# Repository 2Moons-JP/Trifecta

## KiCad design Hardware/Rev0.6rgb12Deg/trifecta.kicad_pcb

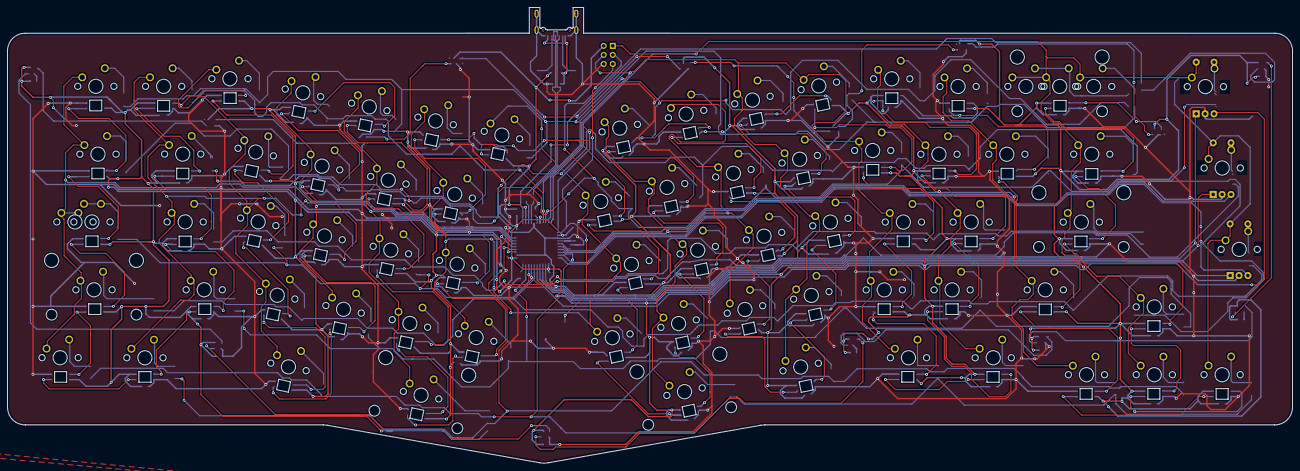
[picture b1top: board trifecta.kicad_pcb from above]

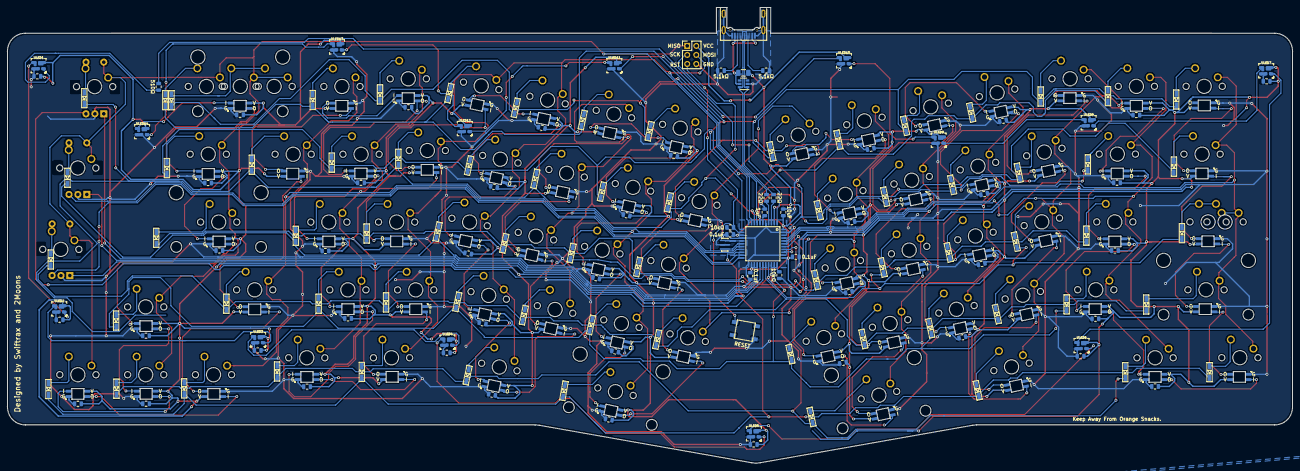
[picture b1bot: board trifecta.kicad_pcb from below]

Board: 2 copper layers, 361.0 x 128.0 mm, 285 parts (210 on the bottom side), 189 nets.

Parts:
C1: 1uF; C_0805_2012Metric
C2, C4, C6, C8, C9, C10, C11, C12, C13, C15, C18, C20, C22, C24, C26, C28, C30, C34, C36, C38, C40, C42, C44, C45, C48, C50, C52, C54, C56, C58, C60, C63, C66, C67, C69, C71, C72, C73, C74, C75, C76, C77, C78, C79: 0.1uF; C_0805_2012Metric
C16: 10uF; C_0805_2012Metric
D_1, D_2, D_3, D_4, D_5, D_6, D_7, D_8, D_9, D_10, D_11, D_12, D_13, D_15, D_16, D_17, D_18, D_19, D_20, D_21, D_22, D_23, D_24, D_25, D_26, D_27, D_28, D_29, D_30, D_31, D_33, D_34, D_35, D_36, D_37, D_38, D_39, D_40, D_41, D_42, D_43, D_44, D_45, D_46, D_47, D_48, D_49, D_50, D_51, D_52, D_53, D_54, D_55, D_56, D_57, D_58, D_59, D_60, D_61, D_62, D_63, D_64, D_65, D_66, D_67, D_68, D_69, D_70, D_71, D_72: D; D3_SMD_v2
F1: 500mA; Fuse_1206_3216Metric
J1: USB2_C_Receptacle; Mid_Mount-USB_C_HandSoldering
J2: ISP Header; PinHeader_2x03_P2.54mm_Vertical
K_1, K_2, K_3, K_4, K_5, K_6, K_7, K_8, K_9, K_10, K_11, K_12, K_13, K_14, K_16, K_18, K_19, K_20, K_21, K_22, K_23, K_24, K_25, K_26, K_27, K_28, K_29, K_30, K_31, K_34, K_35, K_36, K_37, K_38, K_39, K_40, K_41, K_42, K_43, K_44, K_46, K_48, K_49, K_50, K_51, K_52, K_53, K_54, K_55, K_56, K_57, K_58, K_60, K_61, K_70, K_71, K_72: KEYSW; MXOnly-1U-NoLED
K_15: KEYSW; MXOnly-2U-ReversedStabilizers-NoLED
K_17: KEYSW; MXOnly-1.5U-NoLED
K_32, K_33, K_59: KEYSW; MXOnly-1.75U-NoLED
K_45, K_47, K_66: KEYSW; MXOnly-2.25U-ReversedStabilizers-NoLED
K_62, K_63, K_64, K_67, K_68, K_69: KEYSW; MXOnly-1.25U-NoLED
K_65: KEYSW; MXOnly-2.75U-ReversedStabilizers-NoLED
LED1, LED2, LED3, LED4, LED5, LED6, LED7, LED8, LED9, LED10, LED11, LED12, LED13, LED15, LED17, LED18, LED19, LED20, LED21, LED22, LED23, LED24, LED25, LED26, LED27, LED28, LED29, LED30, LED33, LED34, LED35, LED36, LED37, LED38, LED39, LED40, LED41, LED42, LED43, LED44, LED45, LED47, LED48, LED49, LED50, LED51, LED52, LED53, LED54, LED55, LED56, LED57, LED58, LED59, LED60, LED62, LED63, LED64, LED65, LED66, LED67, LED68, LED69, LED70, LED71, LED72: YS-SK6812MINI-E
R1, R6: 10kΩ; R_0805_2012Metric
R2, R3: 5.1kΩ; R_0805_2012Metric
R4, R5: 22Ω; R_0805_2012Metric
R7: 510Ω; R_0805_2012Metric
SW1: RESET; SKQG-1155865
SW2, SW3, SW4: Rotary_Encoder_Switch; RotaryEncoder_EC11
U1: ATmega32U4-AU; ATMEGA32U4-AU
U2: SRV05-4; SOT-23-6
ULED1, ULED2, ULED3, ULED4, ULED5, ULED6, ULED7, ULED8, ULED9, ULED10, ULED11, ULED12, ULED13, ULED14: WS2812B-MINI; SK6812_Mini
Y1: 16MHz; Resonator_SMD_muRata_CSTxExxV-3Pin_3.0x1.1mm_HandSoldering_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

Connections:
0col: J2.1, K_14.1, K_15.1, K_16.1, K_30.1, K_31.1, K_45.1, K_46.1, K_60.1, K_61.1, K_71.1, K_72.1, SW2.S2, SW3.S2, SW4.S2, U1.11
0row: D_31.2, K_31.2, SW2.S1
1row: D_46.2, K_46.2, SW3.S1
2row: D_61.2, K_61.2, SW4.S1
+5V: C2.1, C4.1, C6.1, C8.1, C9.1, C10.1, C11.1, C12.1, C13.1, C15.1, C16.1, C18.1, C20.1, C22.1, C24.1, C26.1, C28.1, C30.1, C34.1, C36.1, C38.1, C40.1, C42.1, C44.1, C45.1, C48.1, C50.1, C52.1, C54.1, C56.1, C58.1, C60.1, C63.1, C66.1, C67.1, C69.1, C71.1, C72.1, C73.1, C74.1, C75.1, C76.1, C77.1, C78.1, C79.1, F1.1, J2.2, LED1.1, LED2.1, LED3.1, LED4.1, LED5.1, LED6.1, LED7.1, LED8.1, LED9.1, LED10.1, LED11.1, LED12.1, LED13.1, LED15.1, LED17.1, LED18.1, LED19.1, LED20.1, LED21.1, LED22.1, LED23.1, LED24.1, LED25.1, LED26.1, LED27.1, LED28.1, LED29.1, LED30.1, LED33.1, LED34.1, LED35.1, LED36.1, LED37.1, LED38.1, LED39.1, LED40.1, LED41.1, LED42.1, LED43.1, LED44.1, LED45.1, LED47.1, LED48.1, LED49.1, LED50.1, LED51.1, LED52.1, LED53.1, LED54.1, LED55.1, LED56.1, LED57.1, LED58.1, LED59.1, LED60.1, LED62.1, LED63.1, LED64.1, LED65.1, LED66.1, LED67.1, LED68.1, LED69.1, LED70.1, LED71.1, LED72.1, R1.1, U1.2, U1.7, U1.14, U1.24, U1.34, U1.44, ULED1.4, ULED2.4, ULED3.4, ULED4.4, ULED5.4, ULED6.4, ULED7.4, ULED8.4, ULED9.4, ULED10.4, ULED11.4, ULED12.4, ULED13.4, ULED14.4
D+: J1.A6, J1.B6, R4.2, U2.6
D-: J1.A7, J1.B7, R5.2, U2.1
ENC0A: SW2.A, U1.25
ENC0B: SW2.B, U1.28
ENC1A: SW3.A, U1.26
ENC1B: SW3.B, U1.21
ENC2A: SW4.A, U1.27
ENC2B: SW4.B, U1.22
GND: C1.2, C2.2, C4.2, C6.2, C8.2, C9.2, C10.2, C11.2, C12.2, C13.2, C15.2, C16.2, C18.2, C20.2, C22.2, C24.2, C26.2, C28.2, C30.2, C34.2, C36.2, C38.2, C40.2, C42.2, C44.2, C45.2, C48.2, C50.2, C52.2, C54.2, C56.2, C58.2, C60.2, C63.2, C66.2, C67.2, C69.2, C71.2, C72.2, C73.2, C74.2, C75.2, C76.2, C77.2, C78.2, C79.2, J1.A1B12, J1.B1A12, J1.S1, J2.6, LED1.3, LED2.3, LED3.3, LED4.3, LED5.3, LED6.3, LED7.3, LED8.3, LED9.3, LED10.3, LED11.3, LED12.3, LED13.3, LED15.3, LED17.3, LED18.3, LED19.3, LED20.3, LED21.3, LED22.3, LED23.3, LED24.3, LED25.3, LED26.3, LED27.3, LED28.3, LED29.3, LED30.3, LED33.3, LED34.3, LED35.3, LED36.3, LED37.3, LED38.3, LED39.3, LED40.3, LED41.3, LED42.3, LED43.3, LED44.3, LED45.3, LED47.3, LED48.3, LED49.3, LED50.3, LED51.3, LED52.3, LED53.3, LED54.3, LED55.3, LED56.3, LED57.3, LED58.3, LED59.3, LED60.3, LED62.3, LED63.3, LED64.3, LED65.3, LED66.3, LED67.3, LED68.3, LED69.3, LED70.3, LED71.3, LED72.3, R2.1, R3.1, R6.1, SW1.1, SW2.C, SW3.C, SW4.C, U1.5, U1.15, U1.23, U1.35, U1.43, U2.2, ULED1.2, ULED2.2, ULED3.2, ULED4.2, ULED5.2, ULED6.2, ULED7.2, ULED8.2, ULED9.2, ULED10.2, ULED11.2, ULED12.2, ULED13.2, ULED14.2, Y1.2
LED: R7.2, U1.1
unnamed: C1.1, U1.6
unnamed: D_1.2, K_1.2
unnamed: D_2.2, K_2.2
unnamed: D_3.2, K_3.2
unnamed: D_4.2, K_4.2
unnamed: D_5.2, K_5.2
unnamed: D_6.2, K_6.2
unnamed: D_7.2, K_7.2
unnamed: D_8.2, K_8.2
unnamed: D_9.2, K_9.2
unnamed: D_10.2, K_10.2
unnamed: D_11.2, K_11.2
unnamed: D_12.2, K_12.2
unnamed: D_13.2, K_13.2
unnamed: D_15.2, K_14.2, K_15.2
unnamed: D_16.2, K_16.2
unnamed: D_17.2, K_17.2
unnamed: D_18.2, K_18.2
unnamed: D_19.2, K_19.2
unnamed: D_20.2, K_20.2
unnamed: D_21.2, K_21.2
unnamed: D_22.2, K_22.2
unnamed: D_23.2, K_23.2
unnamed: D_24.2, K_24.2
unnamed: D_25.2, K_25.2
unnamed: D_26.2, K_26.2
unnamed: D_27.2, K_27.2
unnamed: D_28.2, K_28.2
unnamed: D_29.2, K_29.2
unnamed: D_30.2, K_30.2
unnamed: D_33.2, K_32.2, K_33.2
unnamed: D_34.2, K_34.2
unnamed: D_35.2, K_35.2
unnamed: D_36.2, K_36.2
unnamed: D_37.2, K_37.2
unnamed: D_38.2, K_38.2
unnamed: D_39.2, K_39.2
unnamed: D_40.2, K_40.2
unnamed: D_41.2, K_41.2
unnamed: D_42.2, K_42.2
unnamed: D_43.2, K_43.2
unnamed: D_44.2, K_44.2
unnamed: D_45.2, K_45.2
unnamed: D_47.2, K_47.2
unnamed: D_48.2, K_48.2
unnamed: D_49.2, K_49.2
unnamed: D_50.2, K_50.2
unnamed: D_51.2, K_51.2
unnamed: D_52.2, K_52.2
unnamed: D_53.2, K_53.2
unnamed: D_54.2, K_54.2
unnamed: D_55.2, K_55.2
unnamed: D_56.2, K_56.2
unnamed: D_57.2, K_57.2
unnamed: D_58.2, K_58.2
unnamed: D_59.2, K_59.2
unnamed: D_60.2, K_60.2
unnamed: D_62.2, K_62.2
unnamed: D_63.2, K_63.2
unnamed: D_64.2, K_64.2
unnamed: D_65.2, K_65.2
unnamed: D_66.2, K_66.2
unnamed: D_67.2, K_67.2
unnamed: D_68.2, K_68.2
unnamed: D_69.2, K_69.2
unnamed: D_70.2, K_70.2
unnamed: D_71.2, K_71.2
unnamed: D_72.2, K_72.2
unnamed: J1.A5, R2.2
unnamed: J1.B5, R3.2
unnamed: J2.5, R1.2, SW1.2, U1.13
unnamed: LED1.4, LED17.2
unnamed: LED2.4, LED3.2
unnamed: LED4.4, LED5.2
unnamed: LED6.4, LED7.2
unnamed: LED8.4, LED9.2
unnamed: LED10.2, LED26.4
unnamed: LED10.4, LED11.2
unnamed: LED11.4, LED27.2
unnamed: LED12.2, LED28.4
unnamed: LED12.4, LED13.2
unnamed: LED13.4, LED29.2
unnamed: LED15.2, LED30.4
unnamed: LED15.4, ULED14.1
unnamed: LED17.4, LED33.2
unnamed: LED18.2, LED34.4
unnamed: LED2.2, LED18.4
unnamed: LED3.4, LED19.2
unnamed: LED19.4, LED35.2
unnamed: LED20.2, LED36.4
unnamed: LED4.2, LED20.4
unnamed: LED5.4, LED21.2
unnamed: LED21.4, LED37.2
unnamed: LED22.2, LED38.4
unnamed: LED6.2, LED22.4
unnamed: LED7.4, LED23.2
unnamed: LED23.4, LED39.2
unnamed: LED24.2, LED40.4
unnamed: LED8.2, LED24.4
unnamed: LED9.4, LED25.2
unnamed: LED25.4, LED41.2
unnamed: LED26.2, LED42.4
unnamed: LED27.4, LED43.2
unnamed: LED28.2, LED44.4
unnamed: LED29.4, LED59.2
unnamed: LED30.2, LED45.4
unnamed: LED33.4, LED47.2
unnamed: LED34.2, LED48.4
unnamed: LED35.4, LED49.2
unnamed: LED36.2, LED50.4
unnamed: LED37.4, LED51.2
unnamed: LED38.2, LED52.4
unnamed: LED39.4, LED53.2
unnamed: LED40.2, LED54.4
unnamed: LED41.4, LED55.2
unnamed: LED42.2, LED56.4
unnamed: LED43.4, LED57.2
unnamed: LED44.2, LED58.4
unnamed: LED45.2, LED60.4
unnamed: LED47.4, LED62.2
unnamed: LED48.2, LED63.4
unnamed: LED49.4, LED64.2
unnamed: LED50.2, LED64.4
unnamed: LED51.4, LED65.2
unnamed: LED52.2, LED65.4
unnamed: LED53.4, LED66.2
unnamed: LED54.2, LED66.4
unnamed: LED55.4, LED67.2
unnamed: LED56.2, LED67.4
unnamed: LED57.4, LED68.2
unnamed: LED58.2, LED69.4
unnamed: LED59.4, LED70.2
unnamed: LED60.2, LED71.4
unnamed: LED62.4, LED63.2
unnamed: LED68.4, LED69.2
unnamed: LED70.4, LED72.2
unnamed: LED71.2, LED72.4
unnamed: R4.1, U1.4
unnamed: R5.1, U1.3
unnamed: R6.2, U1.33
unnamed: R7.1, ULED1.3
unnamed: U1.16, Y1.3
unnamed: U1.17, Y1.1
unnamed: ULED1.1, ULED2.3
unnamed: ULED2.1, ULED3.3
unnamed: ULED3.1, ULED4.3
unnamed: ULED4.1, ULED5.3
unnamed: ULED5.1, ULED6.3
unnamed: ULED6.1, ULED7.3
unnamed: ULED7.1, ULED8.3
unnamed: ULED8.1, ULED9.3
unnamed: ULED10.1, ULED11.3
unnamed: ULED9.1, ULED10.3
unnamed: ULED11.1, ULED12.3
unnamed: ULED12.1, ULED13.3
unnamed: ULED13.1, ULED14.3
VBUS: F1.2, J1.A4B9, J1.B4A9, U2.5
col0: K_1.1, K_17.1, K_32.1, K_33.1, K_47.1, K_62.1, U1.41
col1: K_2.1, K_3.1, K_18.1, K_19.1, K_34.1, K_35.1, K_48.1, K_49.1, K_63.1, K_64.1, U1.40
col2: K_4.1, K_5.1, K_20.1, K_21.1, K_36.1, K_37.1, K_50.1, K_51.1, K_65.1, U1.39
col3: K_6.1, K_7.1, K_22.1, K_23.1, K_38.1, K_39.1, K_52.1, K_53.1, U1.38
col4: K_8.1, K_9.1, K_24.1, K_25.1, K_40.1, K_41.1, K_54.1, K_55.1, K_66.1, U1.19
col5: J2.4, K_10.1, K_11.1, K_26.1, K_27.1, K_42.1, K_43.1, K_56.1, K_57.1, K_67.1, K_68.1, U1.10
col6: K_12.1, K_13.1, K_28.1, K_29.1, K_44.1, K_58.1, K_59.1, K_69.1, K_70.1, U1.18
row0: D_2.1, D_4.1, D_6.1, D_8.1, D_10.1, D_12.1, D_15.1, U1.8
row1: D_1.1, D_3.1, D_5.1, D_7.1, D_9.1, D_11.1, D_13.1, D_16.1, U1.12
row2: D_18.1, D_20.1, D_22.1, D_24.1, D_26.1, D_28.1, D_30.1, U1.36
row3: D_17.1, D_19.1, D_21.1, D_23.1, D_25.1, D_27.1, D_29.1, D_31.1, J2.3, U1.9
row4: D_33.1, D_35.1, D_37.1, D_39.1, D_41.1, D_43.1, D_45.1, U1.30
row5: D_34.1, D_36.1, D_38.1, D_40.1, D_42.1, D_44.1, D_46.1, U1.31
row6: D_48.1, D_50.1, D_52.1, D_54.1, D_56.1, D_58.1, D_60.1, U1.32
row7: D_47.1, D_49.1, D_51.1, D_53.1, D_55.1, D_57.1, D_59.1, D_61.1, U1.29
row8: D_63.1, D_65.1, D_67.1, D_69.1, D_71.1, U1.37
row9: D_62.1, D_64.1, D_66.1, D_68.1, D_70.1, D_72.1, U1.20

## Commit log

2021-07-20 7/20
2021-07-21 7/21
